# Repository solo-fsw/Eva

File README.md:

# Eva
Eva is a replacement of PST's SRBox (Serial Response Box) and the parallel port (LPT). It is used for sending or receiving markers. It also processes button responses, which are interpreted as keyboard buttons 1 - 8.

## Response Buttons
Responses from the response buttons are interpreted as keyboard events.
Button1 corresponds to keyboard 1, Button2 to keyboard 2 etc.
There are only events on button presses, not button releases.
Button markers for Biosemi are D8 for Button1, D9 for Button2 etc.
| Button | Keyboard event	| Biosemi marker |
| ------------- | ------------- | ------------- | 
| 1 |	1	| D8 |
| 2	| 2	| D9 |
| 3	| 3	| D10 |
| 4	| 4	| D11 |
| 5	| 5	| D12 |
| 6	| 6	| D13 |
| 7	| 7	| D14 |
| 8	| 8	| D15 |

## Passive/Active data mode
Eva can operate in passive or active data mode.
The main difference is that in active data mode the Biopac connector is **output** for markers. In passive data mode the Biopac connector is **input**.
Active data mode is the normal operation mode, that is used most of the time.

***Active data Mode:***
All markers received over the serial usb port will be set on the Biosemi and Biopac connector.
Eva will set the value off the switches S0-S7 on the Biosemi and Biopac connector when pressing the Trigger button.

***Passive data mode:***
This mode can be handy when you still want to use the parallel port as marker source. The parallel port cable need to be connected to the Biopac connector. Received markers will be send to the Biosemi connector and will be shown on led D0-D7. 
Received markers on serial usb port and markers generated with the S0-S7 will be ignored.
Passive mode will be indicated by the passive red led.

## Switch between passive and active data mode
There are 3 possible options to switch between the active and passive data mode.
- Hold down the trigger button during powering up the Eva, the data mode will be toggled and comfirmed by the led Passive.
- Place Eva in command mode and send an S for passive data mode or A for active data mode.
- When the box detects during boot an high level on bit2 (0x04) it will switch to passive data mode.  

Most parallel ports output bit2 high before initializing, if Eva detects this it’s most likely connected to an parallel port and will switch to input to protect itself.  
Passive mode will be indicated by the passive red led.

## Data and command mode
Data mode is used for sending markers, all the data that is sent over the serial usb connection will be set on the output connectors Biosemi and Biopac.
To put the Eva in data mode open the comport @ 115200 baud, 8 bits, none parity, 1 stop bit (115200,8,N,1).

For switching to command mode open the comport @ 4800 baud (4800,8,N,1).
The red led Cmd will light up when it is in command mode.
 
## Command mode commands
- V - Gives info about Eva. Response is a Json String: *{"Version":"HW1:SW1.2","Serialno":"S01234","Device":"Eva"}*
- S - Puts Eva in passive data mode. Response: *Passive*
- A - Puts Eva in active data mode
- M - Returns the current state of the data mode. Response: *Active*
- P - Pings Eva to see if it’s alive. Response: *Pong,Eva*

Other commands will be ignored. Response: *Unknown command* 

Commands are case sensitive.

## How to use
- In Python, the [marker_management library](https://github.com/solo-fsw/python-markers) can be used. 
- In OpenSesame, the [markers_os4 plugin](https://github.com/solo-fsw/opensesame4_plugin_markers) (for OpenSesame 4) or [markers_os3 plugin](https://github.com/solo-fsw/opensesame3_plugin_markers) (for OpenSesame 3) can be used. 
- In E-Prime, the [Markers package](https://github.com/solo-fsw/eprime_package_markers) can be used.
- In MATLAB, see the [UsbParMarker documentation](https://github.com/solo-fsw/UsbParMarker/tree/main#matlab).

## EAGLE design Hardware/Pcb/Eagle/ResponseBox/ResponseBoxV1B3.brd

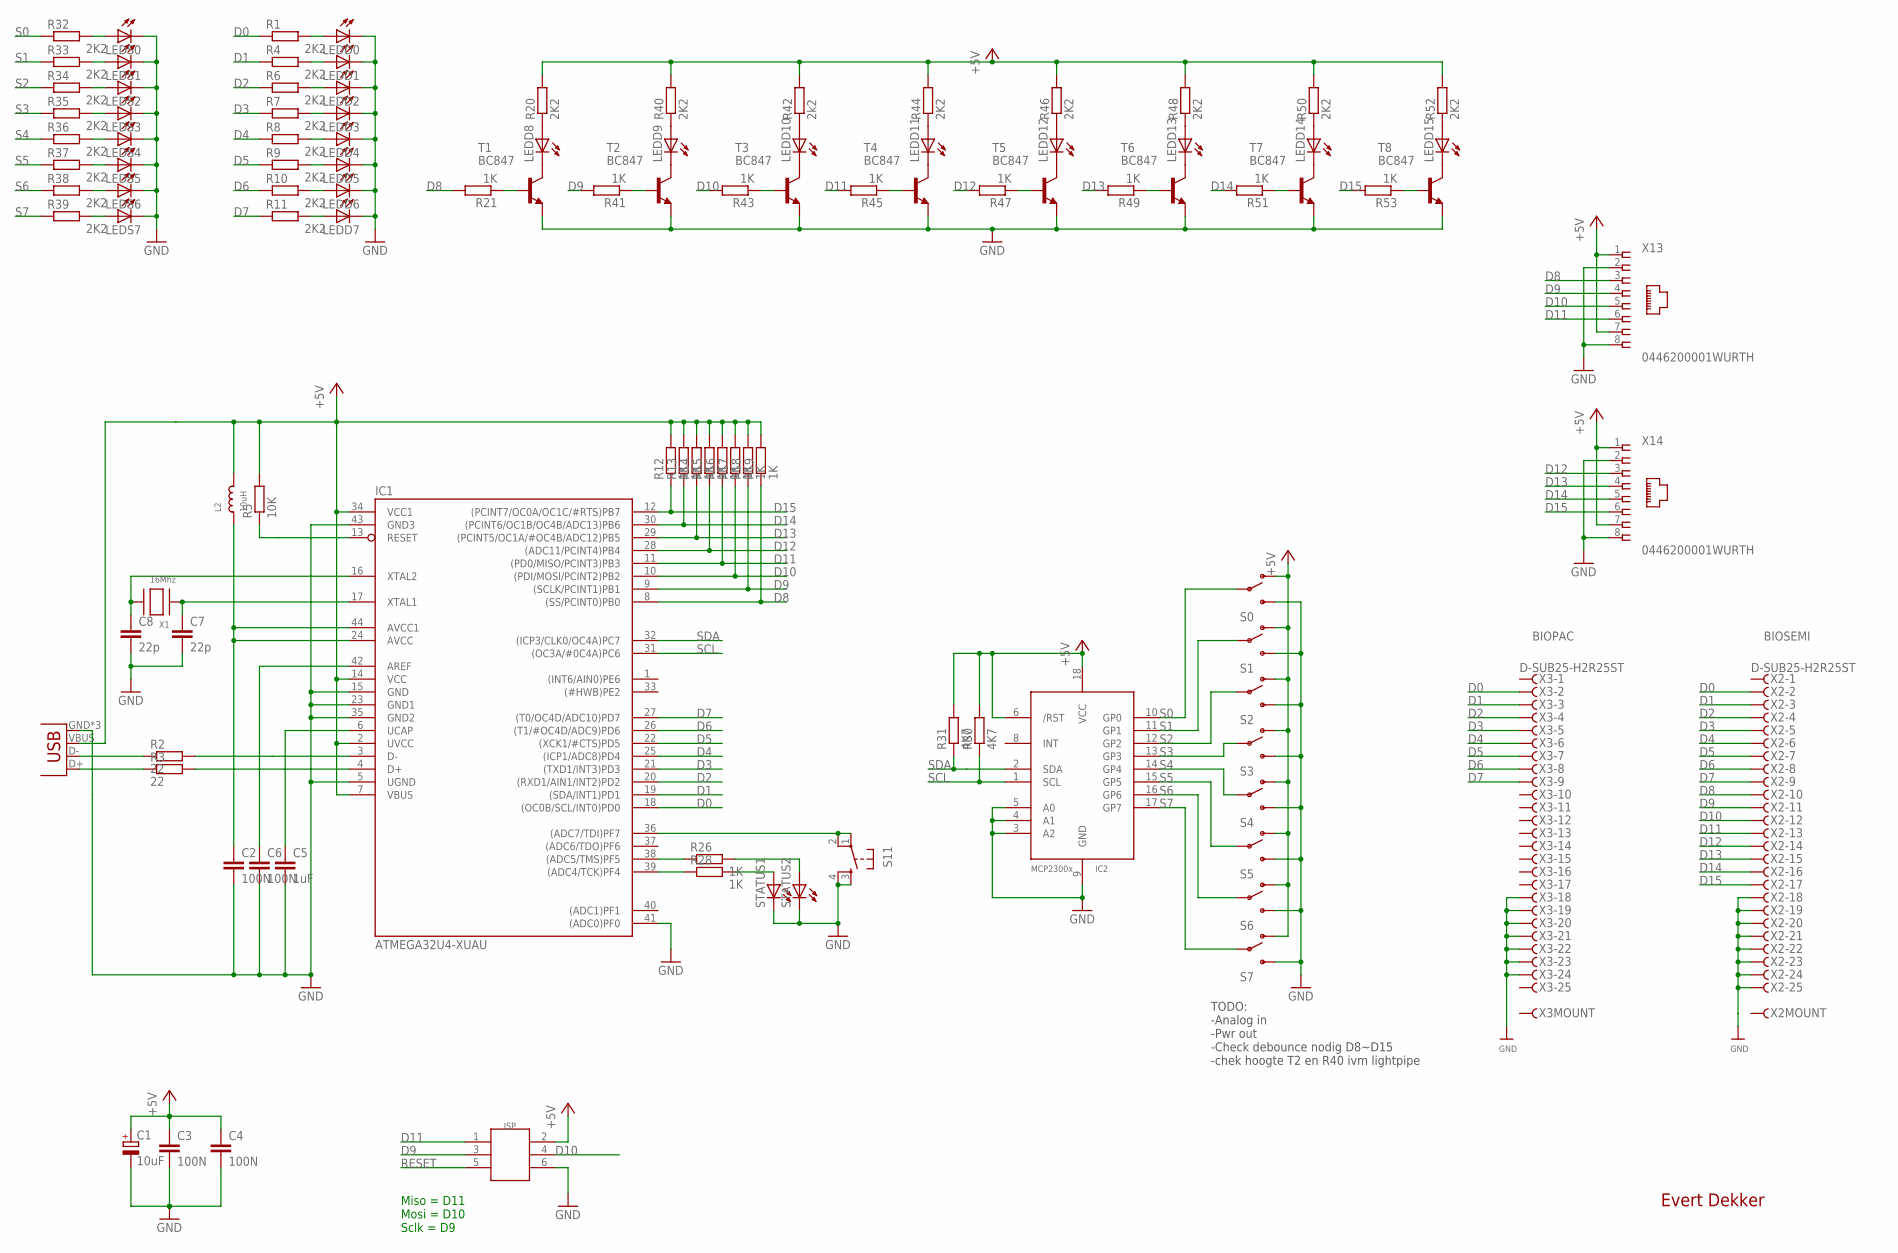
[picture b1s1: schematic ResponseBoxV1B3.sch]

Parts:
C1: 10uF; R/2012-12R; FARNELL 1867958
C2, C3: 100N; C0805; FARNELL 1833888
C4, C6: 100N; C0805
C5: 1uF; C0805; FARNELL 1327700
C7, C8: 22p; C0805; FARNELL 1759489
IC1: ATMEGA32U4-XUAU; TQFP44-PAD; FARNELL 1748525
IC2: MCP2300X/SO; SO18W; FARNELL 1332086
ISP: HEADER-2X3P-SMD; 2X3P-2.54-SMD; FARNELL 9689567
L2: 10uH; 0805; FARNELL 2215650
LEDD0, LEDD1, LEDD8, LEDD9, LEDD10, LEDD11, LEDD12, LEDD13, LEDD14, LEDD15: LEDCHIPLED_0805; CHIPLED_0805
LEDD2, LEDD3, LEDD4, LEDD5, LEDD6: LEDCHIP-LED0805; CHIP-LED0805
LEDD7: LEDCHIP-LED0805; CHIP-LED0805; FARNELL 2062573
LEDS0: LEDCHIPLED_0805; CHIPLED_0805; FARNELL 2062573
LEDS1: LEDCHIPLED_0805; CHIPLED_0805
LEDS2, LEDS3, LEDS4, LEDS5, LEDS6, LEDS7: LEDCHIP-LED0805; CHIP-LED0805
R1, R32: 2K2; R0805; FARNELL 2447686
R2: 22; R0805; FARNELL 2447609
R3: 22; R0805
R4, R6, R7, R8, R9, R10, R11, R20, R33, R34, R35, R36, R37, R38, R39, R40, R44, R46, R48, R50, R52: 2K2; R0805
R5: 10K; R0805; FARNELL 2447553
R12: 1K; R0805; FARNELL 2074332
R13, R14, R15, R16, R17, R18, R19, R21, R26, R28, R41, R43, R45, R47, R49, R51, R53: 1K; R0805
R30: 4K7; R0805; FARNELL 2694141
R31: 4K7; R0805
R42: 2k2; R0805
S0: SWITCH-SPST; SPDT-2MS; FARNELL 9472967
S1, S2, S3, S4, S5, S6, S7: SWITCH-SPST; SPDT-2MS
S11: 10-XX3ESMD; 3ESMD
STATUS1, STATUS2: LEDCHIP-LED0805; CHIP-LED0805
T1: BC847; SOT23; FARNELL 1081230
T2, T3, T4, T5, T6, T7, T8: BC847; SOT23
X1: 16Mhz; NX5032; FARNELL 2467791
X2, X3: D-SUB25-H2R25ST; H2R25ST; FARNELL 2752229
X12: USBPTH-VERTICAL; USB-B-PTH-VERTICAL; FARNELL 1696538
X13, X14: 0446200001WURTH; WURTH-WR-MJ; FARNELL 1841170

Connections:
+5V: C1.+, C3.2, C4.2, IC1.2 (UVCC), IC1.7 (VBUS), IC1.14 (VCC), IC1.34 (VCC1), IC2.6 (/RST), IC2.18 (VCC), ISP.2, L2.2, R5.2, R12.2, R13.2, R14.2, R15.2, R16.2, R17.2, R18.2, R19.2, R20.2, R30.2, R31.2, R40.2, R42.2, R44.2, R46.2, R48.2, R50.2, R52.2, S0.1 (O), S1.1 (O), S2.1 (O), S3.1 (O), S4.1 (O), S5.1 (O), S6.1 (O), S7.1 (O), X12.VBUS, X13.1, X13.7, X14.1, X14.7
D0: IC1.18 ((OC0B/SCL/INT0)PD0), R1.1, X2.2, X3.2
D1: IC1.19 ((SDA/INT1)PD1), R4.1, X2.3, X3.3
D2: IC1.20 ((RXD1/AIN1/INT2)PD2), R6.1, X2.4, X3.4
D3: IC1.21 ((TXD1/INT3)PD3), R7.1, X2.5, X3.5
D4: IC1.25 ((ICP1/ADC8)PD4), R8.1, X2.6, X3.6
D5: IC1.22 ((XCK1/#CTS)PD5), R9.1, X2.7, X3.7
D6: IC1.26 ((T1/#OC4D/ADC9)PD6), R10.1, X2.8, X3.8
D7: IC1.27 ((T0/OC4D/ADC10)PD7), R11.1, X2.9, X3.9
D8: IC1.8 ((SS/PCINT0)PB0), R19.1, R21.2, X2.10, X13.3
D9: IC1.9 ((SCLK/PCINT1)PB1), ISP.3, R18.1, R41.2, X2.11, X13.4
D10: IC1.10 ((PDI/MOSI/PCINT2)PB2), ISP.4, R17.1, R43.2, X2.12, X13.5
D11: IC1.11 ((PD0/MISO/PCINT3)PB3), ISP.1, R16.1, R45.2, X2.13, X13.6
D12: IC1.28 ((ADC11/PCINT4)PB4), R15.1, R47.2, X2.14, X14.3
D13: IC1.29 ((PCINT5/OC1A/#OC4B/ADC12)PB5), R14.1, R49.2, X2.15, X14.4
D14: IC1.30 ((PCINT6/OC1B/OC4B/ADC13)PB6), R13.1, R51.2, X2.16, X14.5
D15: IC1.12 ((PCINT7/OC0A/OC1C/#RTS)PB7), R12.1, R53.2, X2.17, X14.6
D+: IC1.4 (D+), R3.2
D-: IC1.3 (D-), R2.2
GND: C1.-, C2.2, C3.1, C4.1, C5.2, C6.2, C7.2, C8.2, IC1.5 (UGND), IC1.15 (GND), IC1.23 (GND1), IC1.35 (GND2), IC1.41 ((ADC0)PF0), IC1.43 (GND3), IC2.3 (A2), IC2.4 (A1), IC2.5 (A0), IC2.9 (GND), ISP.6, LEDD0.C, LEDD1.C, LEDD2.C, LEDD3.C, LEDD4.C, LEDD5.C, LEDD6.C, LEDD7.C, LEDS0.C, LEDS1.C, LEDS2.C, LEDS3.C, LEDS4.C, LEDS5.C, LEDS6.C, LEDS7.C, S0.3 (S), S1.3 (S), S2.3 (S), S3.3 (S), S4.3 (S), S5.3 (S), S6.3 (S), S7.3 (S), S11.3 (S), S11.4 (S1), STATUS1.C, STATUS2.C, T1.2 (E), T2.2 (E), T3.2 (E), T4.2 (E), T5.2 (E), T6.2 (E), T7.2 (E), T8.2 (E), X2.18, X2.19, X2.20, X2.21, X2.22, X2.23, X2.24, X2.25, X3.18, X3.19, X3.20, X3.21, X3.22, X3.23, X3.24, X12.GND, X12.MP1 (GND), X12.MP2 (GND), X13.2, X13.8, X14.2, X14.8
unnamed: R2.1, X12.D-
unnamed: R3.1, X12.D+
unnamed: LEDD8.A, R20.1
unnamed: LEDD8.C, T1.3 (C)
unnamed: R21.1, T1.1 (B)
unnamed: C2.1, IC1.24 (AVCC), IC1.44 (AVCC1), L2.1
unnamed: LEDD0.A, R1.2
unnamed: LEDD1.A, R4.2
unnamed: IC1.38 ((ADC5/TMS)PF5), R26.1
unnamed: IC1.39 ((ADC4/TCK)PF4), R28.1
unnamed: R26.2, STATUS2.A
unnamed: R28.2, STATUS1.A
unnamed: LEDD2.A, R6.2
unnamed: LEDD3.A, R7.2
unnamed: LEDD4.A, R8.2
unnamed: LEDD5.A, R9.2
unnamed: LEDD6.A, R10.2
unnamed: LEDD7.A, R11.2
unnamed: LEDS0.A, R32.2
unnamed: LEDS1.A, R33.2
unnamed: LEDS2.A, R34.2
unnamed: LEDS3.A, R35.2
unnamed: LEDS4.A, R36.2
unnamed: LEDS5.A, R37.2
unnamed: LEDS6.A, R38.2
unnamed: LEDS7.A, R39.2
unnamed: IC1.36 ((ADC7/TDI)PF7), S11.1, S11.2 (P1)
unnamed: LEDD9.A, R40.1
unnamed: LEDD9.C, T2.3 (C)
unnamed: R41.1, T2.1 (B)
unnamed: LEDD10.A, R42.1
unnamed: LEDD10.C, T3.3 (C)
unnamed: R43.1, T3.1 (B)
unnamed: C6.1, IC1.42 (AREF)
unnamed: C5.1, IC1.6 (UCAP)
unnamed: LEDD11.A, R44.1
unnamed: LEDD11.C, T4.3 (C)
unnamed: R45.1, T4.1 (B)
unnamed: LEDD12.A, R46.1
unnamed: LEDD12.C, T5.3 (C)
unnamed: R47.1, T5.1 (B)
unnamed: LEDD13.A, R48.1
unnamed: LEDD13.C, T6.3 (C)
unnamed: R49.1, T6.1 (B)
unnamed: LEDD14.A, R50.1
unnamed: LEDD14.C, T7.3 (C)
unnamed: R51.1, T7.1 (B)
unnamed: LEDD15.A, R52.1
unnamed: LEDD15.C, T8.3 (C)
unnamed: R53.1, T8.1 (B)
RESET: IC1.13 (RESET), ISP.5, R5.1
S0: IC2.10 (GP0), R32.1, S0.2
S1: IC2.11 (GP1), R33.1, S1.2
S2: IC2.12 (GP2), R34.1, S2.2
S3: IC2.13 (GP3), R35.1, S3.2
S4: IC2.14 (GP4), R36.1, S4.2
S5: IC2.15 (GP5), R37.1, S5.2
S6: IC2.16 (GP6), R38.1, S6.2
S7: IC2.17 (GP7), R39.1, S7.2
SCL: IC1.31 ((OC3A/#0C4A)PC6), IC2.1 (SCL), R30.1
SDA: IC1.32 ((ICP3/CLK0/OC4A)PC7), IC2.2 (SDA), R31.1
XTAL1: C7.1, IC1.17 (XTAL1), X1.P$1
XTAL2: C8.1, IC1.16 (XTAL2), X1.P$2

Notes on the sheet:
Evert Dekker
TODO: -Analog in -Pwr out -Check debounce nodig D8~D15 -chek hoogte T2 en R40 ivm lightpipe
BIOPAC
BIOSEMI
Miso = D11 Mosi = D10 Sclk = D9

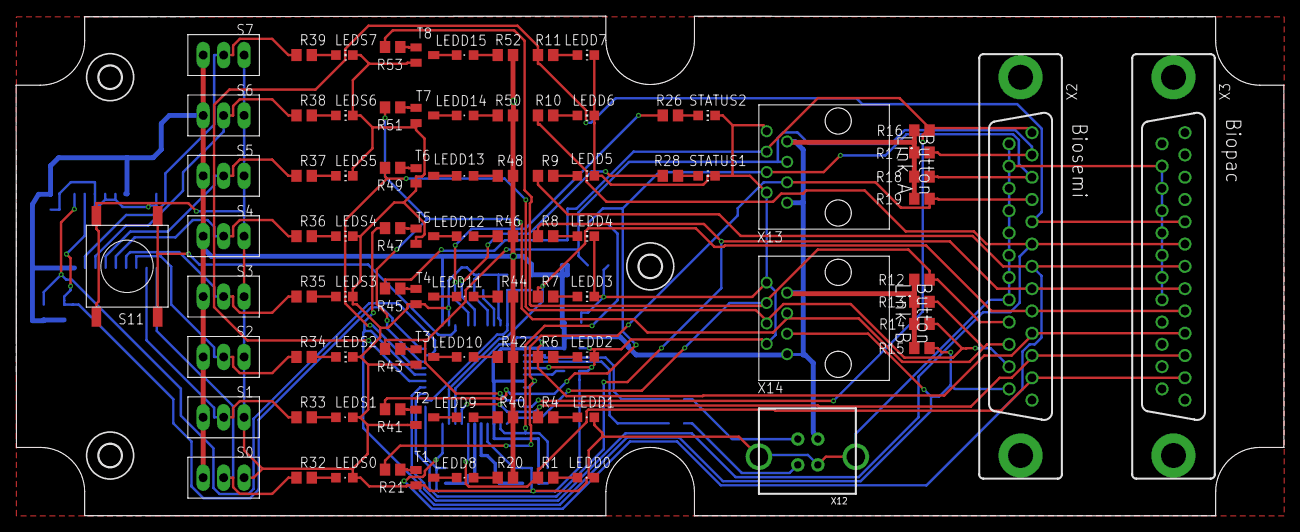
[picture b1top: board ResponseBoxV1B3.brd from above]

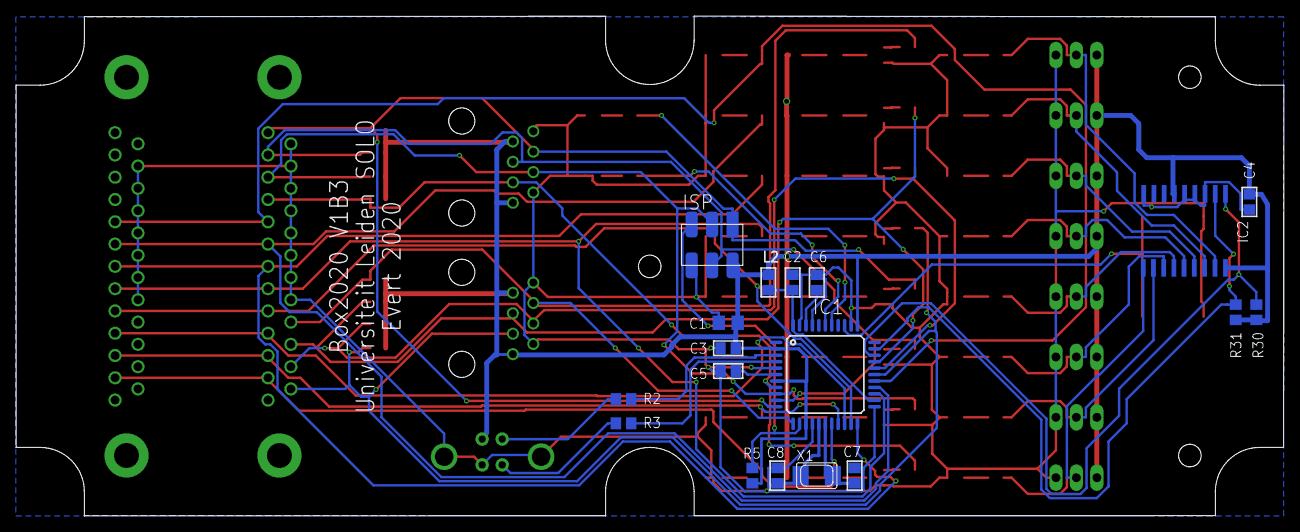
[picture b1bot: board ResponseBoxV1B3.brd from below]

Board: 2 copper layers, 157.5 x 62.1 mm, 111 parts (18 on the bottom side), 83 nets.

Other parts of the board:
U$2, U$4, U$6: MOUNTINGHOLE_2.8

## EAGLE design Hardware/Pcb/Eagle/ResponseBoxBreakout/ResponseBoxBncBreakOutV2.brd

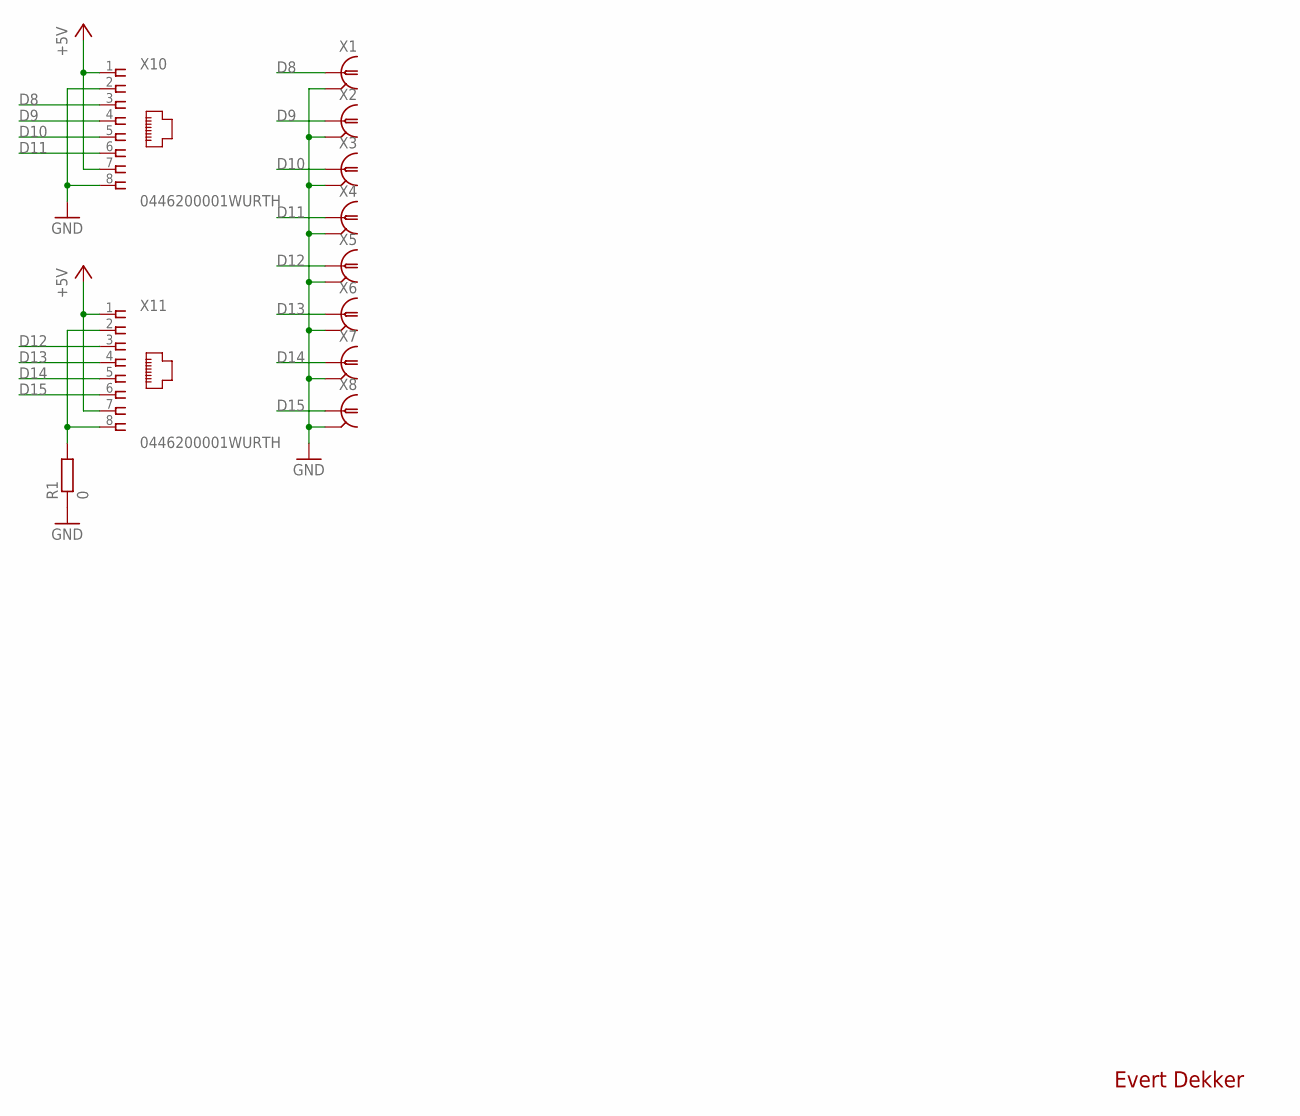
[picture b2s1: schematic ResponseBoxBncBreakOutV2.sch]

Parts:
R1: 0; M0805
X1, X2, X3, X4, X5, X6, X7, X8: R141426
X10, X11: 0446200001WURTH; WURTH-WR-MJ; FARNELL 1841170

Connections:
+5V: X10.1, X10.7, X11.1, X11.7
D8: X1.1, X10.3
D9: X2.1, X10.4
D10: X3.1, X10.5
D11: X4.1, X10.6
D12: X5.1, X11.3
D13: X6.1, X11.4
D14: X7.1, X11.5
D15: X8.1, X11.6
GND: R1.1, X1.2, X1.3 (2), X1.4 (2), X1.5 (2), X2.2, X2.3 (2), X2.4 (2), X2.5 (2), X3.2, X3.3 (2), X3.4 (2), X3.5 (2), X4.2, X4.3 (2), X4.4 (2), X4.5 (2), X5.2, X5.3 (2), X5.4 (2), X5.5 (2), X6.2, X6.3 (2), X6.4 (2), X6.5 (2), X7.2, X7.3 (2), X7.4 (2), X7.5 (2), X8.2, X8.3 (2), X8.4 (2), X8.5 (2), X10.2, X10.8
unnamed: R1.2, X11.2, X11.8

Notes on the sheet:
Evert Dekker

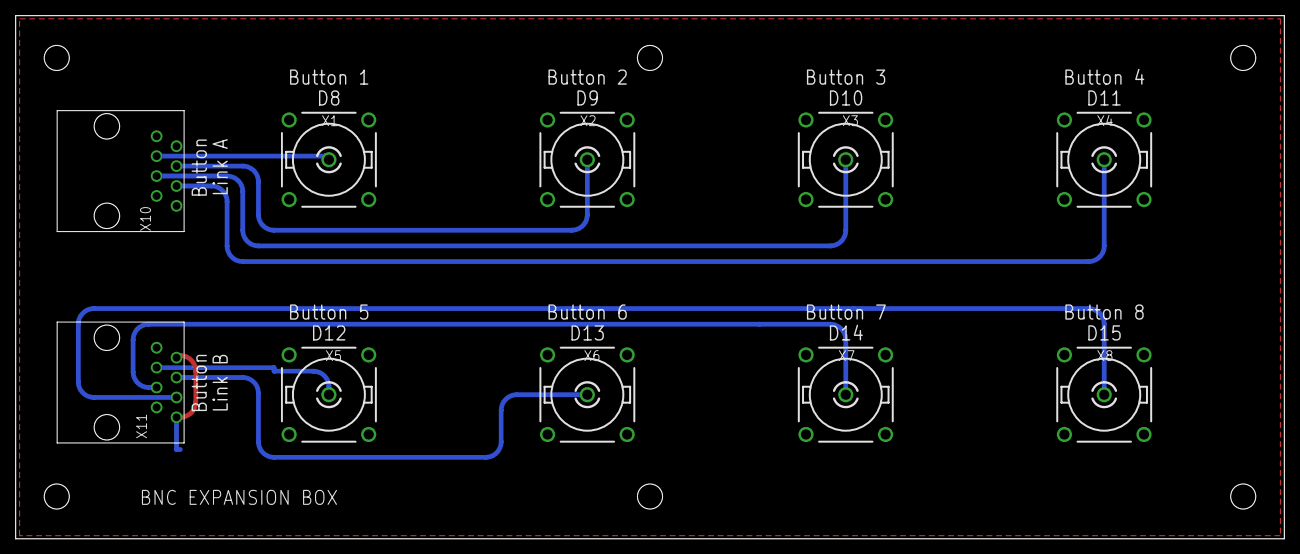
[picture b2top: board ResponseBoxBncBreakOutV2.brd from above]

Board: 2 copper layers, 162.0 x 66.8 mm, 11 parts (1 on the bottom side), 11 nets.

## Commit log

2022-06-17 InitialPush
2022-06-21 Added Eprime Package
2022-07-28 Bug fix slow buttons
    Responsebuton where responding slow after opening and closing the com port. This due some leftover Serial.write for debug purpose in debounceRespButtons()
2022-08-05 Adjusted sample tasks
    Eva_Sample_Task:
    - Includes all package calls
    - Includes use of task events for sending markers
    - Includes instructions
    Eva_Sample_noPackage:
    - All package calls are included as func/sub in script
2022-08-26 Created eva.py
    Initial commit.
    Contains basic eva communication
2022-09-02 Added OpenSesame sample for sending markers to EVA and minor adjustments Python module
2023-02-08 structure update
2023-02-08 folder structure update
2023-02-08 init readme
2023-02-08 update folder structure
2023-02-28 deleted old eva python example
2023-02-28 added info about sample to readme
2023-06-27 removed samples
2023-12-04 Added matlab doc link
2025-04-07 Update Box2020V4.fpd
    Changed text 0X20 to 0x20

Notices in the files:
parts and their libraries:
microbuilder: This work is placed in the public domain, and may be freely used for commercial and non-commercial work with the following conditions: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
SparkFun: Licensing: CC v3.0 Share-Alike You are welcome to use this library for commercial purposes.
